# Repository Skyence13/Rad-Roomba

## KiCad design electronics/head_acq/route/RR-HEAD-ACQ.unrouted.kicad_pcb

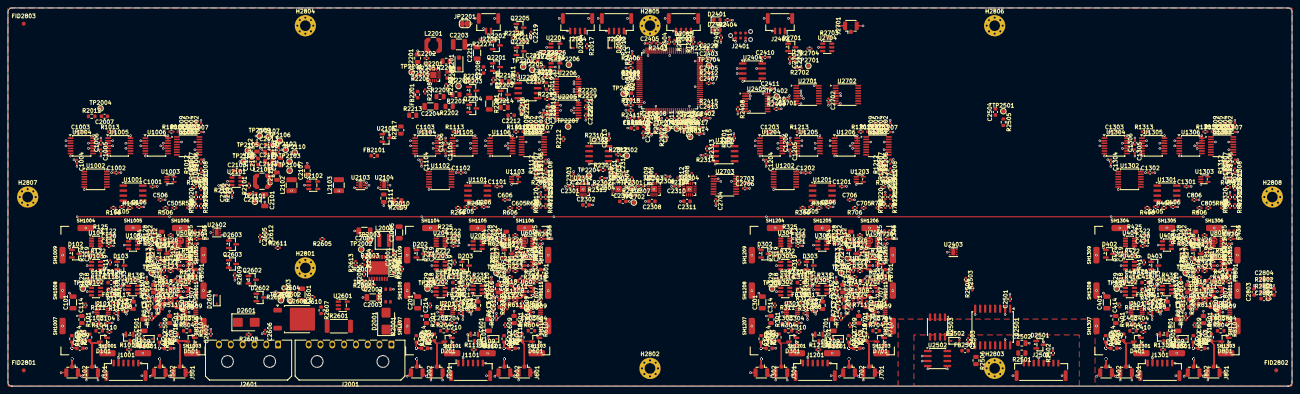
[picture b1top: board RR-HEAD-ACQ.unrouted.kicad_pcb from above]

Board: 6 copper layers, 326.0 x 96.0 mm, 1085 parts (0 on the bottom side), 581 nets.

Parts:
C101, C201, C301, C401, C501, C601, C701, C801, C2204, C2213: 1uF; C_1206_3216Metric
C102, C202, C302, C402, C502, C602, C702, C802, C2001, C2102, C2103, C2205: 100nF; C_0603_1608Metric
C103, C111, C203, C211, C303, C311, C403, C411, C503, C511, C603, C611, C703, C711, C803, C811, C2108, C2406: 4.7uF; C_0603_1608Metric
C104, C105, C106, C107, C108, C113, C114, C115, C118, C120, C121, C122, C125, C126, C127, C204, C205, C206, C207, C208, C213, C214, C215, C218, C220, C221, C222, C225, C226, C227, C304, C305, C306, C307, C308, C313, C314, C315, C318, C320, C321, C322, C325, C326, C327, C404, C405, C406, C407, C408, C413, C414, C415, C418, C420, C421, C422, C425, C426, C427, C504, C505, C506, C507, C508, C513, C514, C515, C518, C520, C521, C522, C604, C605, C606, C607, C608, C613, C614, C615, C618, C620, C621, C622, C704, C705, C706, C707, C708, C713, C714, C715, C718, C720, C721, C722, C804, C805, C806, C807, C808, C813, C814, C815, C818, C820, C821, C822, C1001, C1002, C1003, C1004, C1005, C1006, C1007, C1008, C1009, C1101, C1102, C1103, C1104, C1105, C1106, C1107, C1108, C1109, C1201, C1202, C1203, C1204, C1205, C1206, C1207, C1208, C1209, C1301, C1302, C1303, C1304, C1305, C1306, C1307, C1308, C1309, C2006, C2008, C2009, C2010, C2116, C2202, C2209, C2211, C2216, C2217, C2218, C2219, C2220, C2221, C2222, C2301, C2303, C2304, C2306, C2307, C2309, C2310, C2312, C2313, C2315, C2401, C2402, C2403, C2404, C2405, C2407, C2408, C2409, C2410, C2411, C2412, C2413, C2501, C2503, C2602, C2603, C2606, C2701, C2702, C2703, C2704, C2706: 100nF; C_0402_1005Metric
C109, C209, C309, C409, C509, C609, C709, C809, C1010, C1110, C1210, C1310, C2707, C2708: 100pF; C_0402_1005Metric
C110, C123, C210, C223, C310, C323, C410, C423, C510, C610, C710, C810: 1nF; C_0402_1005Metric
C112, C116, C212, C216, C312, C316, C412, C416, C512, C516, C612, C616, C712, C716, C812, C816, C2109, C2110, C2112, C2201, C2502: 10uF; C_0805_2012Metric
C117, C217, C317, C417, C517, C617, C717, C817: 220pF; C_0402_1005Metric
C119, C219, C319, C419, C519, C619, C719, C819, C2106: 10pF; C_0402_1005Metric
C124, C224, C324, C424: 4.7nF; C_0402_1005Metric
C2002: 22nF; C_0402_1005Metric
C2003, C2004, C2005, C2601: 10uF; C_1206_3216Metric
C2007, C2504, C2801, C2802, C2803, C2804: 10nF; C_0603_1608Metric
C2101: 4.7uF; C_1206_3216Metric
C2104, C2105, C2107, C2111: 22uF; C_0805_2012Metric
C2113, C2115, C2302, C2305, C2308, C2311, C2314: 1uF; C_0603_1608Metric
C2114, C2206, C2207, C2214, C2215, C2604, C2605, C2705: 10nF; C_0402_1005Metric
C2203: 2.2uF; C_1210_3225Metric
C2208: 1nF; C_0603_1608Metric
C2210, C2212: 470nF; C_0603_1608Metric
D101, D201, D301, D401, D501, D601, D701, D801: BAV99; SOT-23
D102, D103, D202, D203, D302, D303, D402, D403, D502, D602, D702, D802, D2603, D2701: BAT54S; SOT-23
D1001, D1101, D1201, D1301, D2002, D2003, D2004, D2502, D2604: PESD5V0S1BA; D_SOD-323
D2001, D2601: SMBJ16A; D_SMB
D2201: PMEG10010ELR; D_SOD-123F
D2202, D2602: BZX84-C12; SOT-23
D2203: BAV199; SOT-23
D2401: green; LED_0603_1608Metric
D2402: red; LED_0603_1608Metric
D2501: SM712; SOT-23
FB101, FB201, FB301, FB401, FB501, FB601, FB701, FB801, FB2101, FB2401: 600R @100MHz; L_0603_1608Metric
FB2201, FB2501: 220R @100MHz; L_0603_1608Metric
FID2801, FID2802, FID2803: fiducial; Fiducial_1mm_Mask2mm
H2801: H1; MountingHole_2.7mm_M2.5_Pad_Via
H2802: H2; MountingHole_2.7mm_M2.5_Pad_Via
H2803: H3; MountingHole_2.7mm_M2.5_Pad_Via
H2804: H4; MountingHole_2.7mm_M2.5_Pad_Via
H2805: H5; MountingHole_2.7mm_M2.5_Pad_Via
H2806: H6; MountingHole_2.7mm_M2.5_Pad_Via
H2807: H7; MountingHole_2.7mm_M2.5_Pad_Via
H2808: H8; MountingHole_2.7mm_M2.5_Pad_Via
J101, J102, J201, J202, J301, J302, J401, J402, J501, J502, J601, J602, J701, J702, J801, J802, J2701: U.FL; U.FL_Hirose_U.FL-R-SMT-1_Vertical
J1001, J1101, J1201, J1301: GH-6; JST_GH_SM06B-GHS-TB_1x06-1MP_P1.25mm_Horizontal
J2001: Micro-Fit 3.0 1x8 RA; Molex_Micro-Fit_3.0_43650-0800_1x08_P3.00mm_Horizontal
J2002, J2003, J2004: GH-4; JST_GH_SM04B-GHS-TB_1x04-1MP_P1.25mm_Horizontal
J2201: GH-2; JST_GH_SM02B-GHS-TB_1x02-1MP_P1.25mm_Horizontal
J2401: TC2030-NL; Tag-Connect_TC2030-IDC-NL_2x03_P1.27mm_Vertical
J2402: GH-3; JST_GH_SM03B-GHS-TB_1x03-1MP_P1.25mm_Horizontal
J2501: GH-8; JST_GH_SM08B-GHS-TB_1x08-1MP_P1.25mm_Horizontal
J2601: Micro-Fit 3.0 1x6 RA; Molex_Micro-Fit_3.0_43650-0600_1x06_P3.00mm_Horizontal
JP2201: open; SolderJumper-2_P1.3mm_Open_RoundedPad1.0x1.5mm
L2001: 900R CM; L_CommonMode_TDK_ACM4520
L2002: 10uH; L_Coilcraft_XAL4040-XXX
L2101, L2201: 10uH; L_Coilcraft_LPS4018
L2102, L2103: 10uH; L_1210_3225Metric
Q1001, Q1101, Q1201, Q1301, Q2205, Q2602: BSS138; SOT-23
Q2201, Q2203, Q2204: BSS123; SOT-23
Q2202: MMBTA42; SOT-23
Q2601: SUD50P04-08; TO-252-2
Q2603: MMBT3904; SOT-23
R101, R201, R301, R401, R501, R601, R701, R801: 1k; R_0805_2012Metric
R102, R202, R302, R402, R502, R602, R702, R802: 100R; R_0603_1608Metric
R103, R104, R203, R204, R303, R304, R403, R404, R503, R504, R603, R604, R703, R704, R803, R804: 20R; R_0603_1608Metric
R105, R205, R305, R405, R505, R605, R705, R805: 4.99k; R_0402_1005Metric
R106, R206, R306, R406, R506, R606, R706, R806: 220k; R_0402_1005Metric
R107, R109, R115, R119, R125, R126, R127, R129, R134, R135, R207, R209, R215, R219, R225, R226, R227, R229, R234, R235, R307, R309, R315, R319, R325, R326, R327, R329, R334, R335, R407, R409, R415, R419, R425, R426, R427, R429, R434, R435, R507, R509, R515, R519, R525, R526, R527, R607, R609, R615, R619, R625, R626, R627, R707, R709, R715, R719, R725, R726, R727, R807, R809, R815, R819, R825, R826, R827, R1015, R1115, R1215, R1315, R2013, R2015, R2017, R2207, R2220, R2404, R2405, R2602, R2605, R2701, R2704: 1k; R_0402_1005Metric
R108, R130, R208, R230, R308, R330, R408, R430, R508, R608, R708, R808, R1013, R1014, R1016, R1018, R1113, R1114, R1116, R1118, R1213, R1214, R1216, R1218, R1313, R1314, R1316, R1318, R2011, R2014, R2016, R2018, R2103, R2206, R2210, R2211, R2216, R2222, R2224, R2226, R2228, R2229, R2231, R2302, R2304, R2306, R2308, R2310, R2313, R2314, R2401, R2409, R2410, R2411, R2412, R2503, R2504, R2606, R2613: 10k; R_0402_1005Metric
R110, R113, R121, R128, R210, R213, R221, R228, R310, R313, R321, R328, R410, R413, R421, R428, R510, R513, R521, R528, R610, R613, R621, R628, R710, R713, R721, R728, R810, R813, R821, R828, R1017, R1019, R1117, R1119, R1217, R1219, R1317, R1319: 100R; R_0402_1005Metric
R111, R211, R311, R411, R511, R611, R711, R811, R2703: 49.9R; R_0402_1005Metric
R112, R212, R312, R412, R512, R612, R712, R812, R1002, R1004, R1006, R1008, R1010, R1011, R1012, R1020, R1102, R1104, R1106, R1108, R1110, R1111, R1112, R1120, R1202, R1204, R1206, R1208, R1210, R1211, R1212, R1220, R1302, R1304, R1306, R1308, R1310, R1311, R1312, R1320, R2008, R2101, R2212, R2227, R2230, R2309, R2315, R2316, R2403, R2408, R2413, R2414, R2415, R2416, R2417, R2608, R2610, R2612, R2702: 100k; R_0402_1005Metric
R114, R214, R314, R414, R514, R614, R714, R814: 22R; R_0402_1005Metric
R116, R122, R132, R216, R222, R232, R316, R322, R332, R416, R422, R432, R516, R522, R616, R622, R716, R722, R816, R822: 499R; R_0402_1005Metric
R117, R123, R217, R223, R317, R323, R417, R423, R517, R523, R617, R623, R717, R723, R817, R823: 24.9R; R_0402_1005Metric
R118, R218, R318, R418, R518, R618, R718, R818: 453R; R_0402_1005Metric
R120, R220, R320, R420, R520, R620, R720, R820: 226R; R_0402_1005Metric
R124, R133, R224, R233, R324, R333, R424, R433, R524, R624, R724, R824, R2301, R2303, R2305, R2307: 330R; R_0402_1005Metric
R131, R231, R331, R431: 2k; R_0402_1005Metric
R1001, R1003, R1005, R1007, R1009, R1101, R1103, R1105, R1107, R1109, R1201, R1203, R1205, R1207, R1209, R1301, R1303, R1305, R1307, R1309: 47R; R_0402_1005Metric
R2001: 4.7k; R_0603_1608Metric
R2002: 866k; R_0603_1608Metric
R2003: 68.1k; R_0402_1005Metric
R2004: 66.5k; R_0402_1005Metric
R2005: 12k; R_0402_1005Metric
R2006: 30.1k; R_0402_1005Metric
R2007, R2502: 0R; R_0402_1005Metric
R2009: 1R; R_0805_2012Metric
R2010: 56k; R_0402_1005Metric
R2012, R2505, R2802: 1M; R_0603_1608Metric
R2019: 1k; R_0603_1608Metric
R2102: 60.4k; R_0402_1005Metric
R2201, R2202: 1.07M; R_0805_2012Metric
R2203: 71.5k; R_0402_1005Metric
R2204: 100R; R_0805_2012Metric
R2205: 49.9k; R_0402_1005Metric
R2208: 2.49k; R_0402_1005Metric
R2209: 470k; R_0805_2012Metric
R2213, R2214: 1.2M; R_0805_2012Metric
R2215: 100k; R_0603_1608Metric
R2217, R2218: 4.99M; R_0805_2012Metric
R2219: 412k; R_0402_1005Metric
R2221: 47k; R_1206_3216Metric
R2223: 7.15k; R_0402_1005Metric
R2225: 18.7k; R_0402_1005Metric
R2311: 3.16k; R_0402_1005Metric
R2312: 10R; R_0402_1005Metric
R2402: 33R; R_0402_1005Metric
R2406, R2407: 2.2k; R_0402_1005Metric
R2501, R2506: 120R; R_0805_2012Metric
R2601: 10mR; R_2512_6332Metric
R2603: 68k; R_0402_1005Metric
R2604, R2609: 47k; R_0402_1005Metric
R2607: 47k; R_0603_1608Metric
R2611: 33k; R_0402_1005Metric
R2801: 0R; R_0603_1608Metric
RT2201: 10k NTC; R_0402_1005Metric
SH1001, SH1002, SH1003, SH1004, SH1005, SH1006, SH1007, SH1008, SH1009, SH1010, SH1011, SH1012, SH1101, SH1102, SH1103, SH1104, SH1105, SH1106, SH1107, SH1108, SH1109, SH1110, SH1111, SH1112, SH1201, SH1202, SH1203, SH1204, SH1205, SH1206, SH1207, SH1208, SH1209, SH1210, SH1211, SH1212, SH1301, SH1302, SH1303, SH1304, SH1305, SH1306, SH1307, SH1308, SH1309, SH1310, SH1311, SH1312: shield clip; Harwin_S1711-46R_ShieldClip
SH1013, SH1113, SH1213, SH1313: lane shield can; RR-HEAD-SHLD-A_LaneShieldCan
TP101: F0 PRE; TestPoint_Pad_D1.0mm
TP201: F1 PRE; TestPoint_Pad_D1.0mm
TP301: F2 PRE; TestPoint_Pad_D1.0mm
TP401: F3 PRE; TestPoint_Pad_D1.0mm
TP501: R0 PRE; TestPoint_Pad_D1.0mm
TP601: R1 PRE; TestPoint_Pad_D1.0mm
TP701: R2 PRE; TestPoint_Pad_D1.0mm
TP801: R3 PRE; TestPoint_Pad_D1.0mm
TP2001: EF_IMON; TestPoint_Pad_D1.0mm
TP2002: EF_SHDN; TestPoint_Pad_D1.0mm
TP2003: EF_MODE; TestPoint_Pad_D1.0mm
TP2004: J1 SHIELD; TestPoint_Pad_D1.0mm
TP2101: VIN_F; TestPoint_Pad_D1.0mm
TP2102: +5V6; TestPoint_Pad_D1.0mm
TP2103: +5V_A; TestPoint_Pad_D1.0mm
TP2104: +3V3; TestPoint_Pad_D1.0mm
TP2105: +3V3_EVT; TestPoint_Pad_D1.0mm
TP2106: VREF_ADC; TestPoint_Pad_D1.0mm
TP2107, TP2108, TP2109, TP2110: GND; TestPoint_Pad_D1.0mm
TP2201: HV_MON2; TestPoint_Pad_D1.0mm
TP2202: HV_BUS; TestPoint_Pad_D1.0mm
TP2203: HV_RAW; TestPoint_Pad_D1.0mm
TP2204: HV_SET; TestPoint_Pad_D1.0mm
TP2205: HV_DRV; TestPoint_Pad_D1.0mm
TP2206: HV_INH_N; TestPoint_Pad_D1.0mm
TP2207: HV_PERMIT; TestPoint_Pad_D1.0mm
TP2208: BIAS_VMON; TestPoint_Pad_D1.0mm
TP2209: BIAS_IMON; TestPoint_Pad_D1.0mm
TP2301: DAC1 OUT7; TestPoint_Pad_D1.0mm
TP2302: VBL; TestPoint_Pad_D1.0mm
TP2401: BOOT0; TestPoint_Pad_D1.0mm
TP2402: EXP P7; TestPoint_Pad_D1.0mm
TP2403: SYNC_IN; TestPoint_Pad_D1.0mm
TP2501: J2 SHIELD; TestPoint_Pad_D1.0mm
TP2601: HTR_SW; TestPoint_Pad_D1.0mm
TP2602: HTR_GATE; TestPoint_Pad_D1.0mm
TP2701: MON_BUS; TestPoint_Pad_D1.0mm
TP2702: PULSER_AMPL; TestPoint_Pad_D1.0mm
TP2703: PULSER_STROBE; TestPoint_Pad_D1.0mm
TP2704: LATCH_TEST; TestPoint_Pad_D1.0mm
U101, U201, U301, U401, U501, U601, U701, U801: 74LVC2G53; VSSOP-8_2.3x2mm_P0.5mm
U102, U103, U202, U203, U302, U303, U402, U403, U502, U503, U602, U603, U702, U703, U802, U803: OPA838; SOT-23-6
U104, U204, U304, U404, U504, U604, U704, U804: TLV3502; SOT-23-8
U105, U205, U305, U405, U2704: OPA836; SOT-23-6
U106, U206, U306, U406: TLV3501; SOT-23-6
U1001, U1101, U1201, U1301, U2305, U2306: TLV9062; SOIC-8_3.9x4.9mm_P1.27mm
U1002, U1102, U1202, U1302: 74LVC32A; TSSOP-14_4.4x5mm_P0.65mm
U1003, U1103, U1203, U1303: 74LVC1G32; SOT-353_SC-70-5
U1004, U1005, U1006, U1104, U1105, U1106, U1204, U1205, U1206, U1304, U1305, U1306, U2205: 74LVC74A; TSSOP-14_4.4x5mm_P0.65mm
U1007, U1107, U1207, U1307, U2703: TMUX1108; TSSOP-16_4.4x5mm_P0.65mm
U2001: TPS26600; HTSSOP-16-1EP_4.4x5mm_P0.65mm_EP3.4x5mm
U2101: LMR51606YF; SOT-23-6
U2102: TPS7A2050; SOT-23-5
U2103, U2104: TLV76733; WSON-6-1EP_2x2mm_P0.65mm_EP1x1.6mm
U2105: REF3030; SOT-23
U2201: TPS61391; WQFN-16-1EP_3x3mm_P0.5mm_EP1.6x1.6mm
U2202: OPA2333; SOIC-8_3.9x4.9mm_P1.27mm
U2203, U2204: TLV7021; SOT-23-5
U2206: 74LVC00A; TSSOP-14_4.4x5mm_P0.65mm
U2301, U2302, U2303, U2304: DAC60508Z; WQFN-16-1EP_3x3mm_P0.5mm_EP1.6x1.6mm
U2401: STM32G474VET6; LQFP-100_14x14mm_P0.5mm
U2402, U2403: TMP117; WSON-6-1EP_2x2mm_P0.65mm_EP1x1.6mm
U2404: 24AA025E64; SOIC-8_3.9x4.9mm_P1.27mm
U2405: TCA9534; TSSOP-16_4.4x5mm_P0.65mm
U2501: ISO1430B; SOIC-16W_7.5x10.3mm_P1.27mm
U2502: THVD1420; SOIC-8_3.9x4.9mm_P1.27mm
U2503: ISO7710; SOIC-8_3.9x4.9mm_P1.27mm
U2601: INA180A2; SOT-23-5
U2701: 74HC238; TSSOP-16_4.4x5mm_P0.65mm
U2702: 74LVC138A; TSSOP-16_4.4x5mm_P0.65mm
Y2401: 24.000 MHz TCXO; Oscillator_SMD_ECS_2520MV-xxx-xx-4Pin_2.5x2.0mm

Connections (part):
+3V3: C2110.1, C2216.1, C2217.1, C2220.1, C2221.1, C2303.1, C2306.1, C2309.1, C2312.1, C2401.1, C2402.1, C2403.1, C2404.1, C2405.1, C2406.1, C2410.1, C2411.1, C2412.1, C2413.1, C2501.1, C2602.1, C2701.1, D2603.2, FB2101.1, FB2201.1, FB2401.1, J2401.1, R1017.1, R1117.1, R1217.1, R1317.1, R2008.1, R2014.1, R2016.1, R2018.1, R2226.1, R2227.1, R2302.1, R2304.1, R2306.1, R2308.1, R2309.1, R2403.1, R2404.1, R2405.1, R2406.1, R2407.1, R2503.1, TP2104.1, U2103.1, U2103.2, U2203.5, U2204.5, U2205.2, U2205.4, U2205.10, U2205.13, U2205.14, U2206.14, U2301.16, U2302.16, U2303.16, U2304.16, U2401.6, U2401.24, U2401.49, U2401.64, U2401.75, U2401.100, U2402.5, U2403.4, U2403.5, U2404.8, U2405.16, U2501.1, U2503.8, U2601.5, U2701.6, U2701.16, U2703.2
+3V3A: C2113.1, C2114.1, C2407.1, D2701.2, FB2101.2, U2105.1, U2401.37
+3V3_EVT: C107.1, C122.1, C127.1, C207.1, C222.1, C227.1, C307.1, C322.1, C327.1, C407.1, C422.1, C427.1, C507.1, C522.1, C607.1, C622.1, C707.1, C722.1, C807.1, C822.1, C1002.1, C1003.1, C1004.1, C1005.1, C1006.1, C1102.1, C1103.1, C1104.1, C1105.1, C1106.1, C1202.1, C1203.1, C1204.1, C1205.1, C1206.1, C1302.1, C1303.1, C1304.1, C1305.1, C1306.1, C2112.1, C2702.1, D102.2, D103.2, D202.2, D203.2, D302.2, D303.2, D402.2, D403.2, D502.2, D602.2, D702.2, D802.2, TP2105.1, U101.8, U104.8, U106.4, U201.8, U204.8, U206.4, U301.8, U304.8, U306.4, U401.8, U404.8, U406.4, U501.8, U504.8, U601.8, U604.8, U701.8, U704.8, U801.8, U804.8, U1002.14, U1003.5, U1004.2, U1004.4, U1004.10, U1004.12, U1004.14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
+3V3_HV: C2201.1, C2202.1, FB2201.2, L2201.1, U2201.10, U2201.14, U2201.15
+5V6: C2104.1, C2105.1, C2106.1, C2109.1, L2101.2, L2102.1, L2103.1, R2102.1, TP2102.1, U2103.4, U2103.6
+5V6_A: C2107.1, L2102.2, U2102.1, U2102.3
+5V6_E: C2111.1, L2103.2, U2104.4, U2104.6
+5V_A: C1001.1, C1007.1, C1101.1, C1107.1, C1201.1, C1207.1, C1301.1, C1307.1, C2108.1, C2209.1, C2302.1, C2305.1, C2308.1, C2311.1, C2313.1, C2315.1, C2703.1, C2706.1, D101.2, D201.2, D301.2, D401.2, D501.2, D601.2, D701.2, D801.2, D2203.2, FB101.1, FB201.1, FB301.1, FB401.1, FB501.1, FB601.1, FB701.1, FB801.1, R2224.1, TP2103.1, U1001.8, U1007.13, U1101.8, U1107.13, U1201.8, U1207.13, U1301.8, U1307.13, U2102.5, U2202.8, U2301.7, U2302.7, U2303.7, U2304.7, U2305.8, U2306.8, U2703.13, U2704.5, U2704.6
ALPHA_F0: R1005.2, R1006.1, U2401.86
ALPHA_F1: R1105.2, R1106.1, U2401.87
ALPHA_F2: R1205.2, R1206.1, U2401.88
ALPHA_F3: R1305.2, R1306.1, U2401.89
BIAS_IMON: C2207.1, R2207.2, TP2209.1, U2401.25
BIAS_IMON_R: C2206.1, R2206.1, R2207.1, U2201.4
BIAS_VMON: C2215.1, R2220.2, TP2208.1, U2401.22
BIAS_VMON_B: R2220.1, U2202.6, U2202.7, U2203.4
BK_CB: C2103.1, U2101.1
BK_EN: R2101.2, U2101.4
BK_FB: C2106.2, R2102.2, R2103.1, U2101.3
BK_SW: C2103.2, L2101.1, U2101.6
BOOT0: R2401.1, TP2401.1, U2401.95
BUMP_ZONE_F_N: C2008.1, R2013.2, R2014.2, U2401.7
BUMP_ZONE_L_N: C2009.1, R2015.2, R2016.2, U2401.8
BUMP_ZONE_R_N: C2010.1, R2017.2, R2018.2, U2401.9
BUSY_F0: R1001.2, R1002.1, U2401.78
BUSY_F1: R1101.2, R1102.1, U2401.90
BUSY_F2: R1201.2, R1202.1, U2401.47
BUSY_F3: R1301.2, R1302.1, U2401.50
BUSY_R0: R1007.2, R1008.1, U2401.20
BUSY_R1: R1107.2, R1108.1, U2401.21
BUSY_R2: R1207.2, R1208.1, U2401.39
BUSY_R3: R1307.2, R1308.1, U2401.40
BUS_5V: D2502.1, FB2501.1, J2501.3
BUS_5VF: C2502.1, C2503.1, FB2501.2, U2501.16, U2502.8, U2503.1
BUS_GND: C2502.2, C2503.2, D2501.3, D2502.2, J2501.4, J2501.MP, R2502.2, U2501.9, U2501.15, U2502.2, U2502.3, U2502.4, U2502.5, U2503.4
BZ_F_IN: D2002.1, J2002.3, R2013.1
BZ_L_IN: D2003.1, J2003.3, R2015.1
BZ_R_IN: D2004.1, J2004.3, R2017.1
CLR_F0_N: R1013.1, U1004.1, U1004.13, U1005.1, U2401.97
CLR_F1_N: R1113.1, U1104.1, U1104.13, U1105.1, U2401.98
CLR_F2_N: R1213.1, U1204.1, U1204.13, U1205.1, U2401.5
CLR_F3_N: R1313.1, U1304.1, U1304.13, U1305.1, U2401.38
CLR_R0_N: R1014.1, U1005.13, U1006.1, U2401.41
CLR_R1_N: R1114.1, U1105.13, U1106.1, U2401.42
CLR_R2_N: R1214.1, U1205.13, U1206.1, U2401.43
CLR_R3_N: R1314.1, U1305.13, U1306.1, U2401.44
DAC0_REF: C2301.1, U2301.1
DAC0_SDO: R2301.1, U2301.15
DAC1_REF: C2304.1, U2302.1, U2305.3
DAC1_SDO: R2303.1, U2302.15
DAC1_SPARE: TP2301.1, U2302.11
DAC2_REF: C2307.1, U2303.1
DAC2_SDO: R2305.1, U2303.15
DAC3_REF: C2310.1, U2304.1
DAC3_SDO: R2307.1, U2304.15
DAC_CS0_N: R2302.2, U2301.12, U2401.26
DAC_CS1_N: R2304.2, U2302.12, U2401.31
DAC_CS2_N: R2306.2, U2303.12, U2401.34
DAC_CS3_N: R2308.2, U2304.12, U2401.66
DAC_MISO: R2301.2, R2303.2, R2305.2, R2307.2, R2309.2, U2401.28
DAC_MOSI: U2301.14, U2302.14, U2303.14, U2304.14, U2401.29
DAC_SCK: U2301.13, U2302.13, U2303.13, U2304.13, U2401.27
DBG_RX: J2402.2, R2403.2, U2401.80
DBG_TX: J2402.1, U2401.79
EF_DVDT: C2002.1, U2001.12
EF_FLT_N: R2008.2, U2001.14, U2405.9
EF_ILIM: R2005.1, U2001.11
EF_IMON: R2006.1, TP2001.1, U2001.10
EF_MODE: R2007.1, TP2003.1, U2001.6
EF_OVP: R2003.2, R2004.1, U2001.5
EF_RTN: C2002.2, R2004.2, R2005.2, R2006.2, R2007.2, U2001.8, U2001.17
EF_SHDN: TP2002.1, U2001.7
EF_UVLO: R2002.2, R2003.1, U2001.3
EXP_P7: TP2402.1, U2405.12
F0_A: C109.2, C110.2, D101.3, J101.1, R103.1, R104.1, R114.1
F0_CALPHA: U106.5, U1002.9
F0_CLLD: R128.1, U104.7, U1002.1
F0_CULD: U104.6, U1002.4
F0_FAST: C119.1, R122.1, R124.1, U103.1
F0_FCMP: D102.3, R124.2, R125.1, U104.1, U104.3
F0_FFB: C119.2, R122.2, R123.1, U103.4
F0_FS: C117.2, R120.2, R121.1, U103.3
F0_HV1: C101.1, R101.2, R102.1
F0_HVF: C102.1, J102.1, R102.2
F0_KALPHA: U1002.8, U1005.3
F0_KLLD: U1002.3, U1004.3
F0_KULD: U1002.6, U1004.11
F0_MFAST: R125.2, U1007.4
F0_MPRE: R119.2, U1007.12
F0_MSLOW: R134.2, U1007.6
F0_PFB: R116.2, R117.1, U102.4
F0_PG: C116.1, R117.2
F0_PIN: C114.2, R115.1, U102.3
F0_PINA: C114.1, R114.2
F0_PRE: C117.1, R116.1, R118.1, R119.1, R120.1, R129.1, U102.1
F0_PRE_TP: R118.2, TP101.1
F0_SCMP: D103.3, R133.2, R134.1, U106.3
F0_SFB: R131.2, R132.1, U105.4
F0_SI: C123.1, C124.1, R129.2
F0_SLOW: R131.1, R133.1, U105.1
F0_SS: C124.2, R130.1, U105.3
F0_TA: C126.1, R135.2, U106.1
F0_TL: C120.1, R126.2, U104.2
F0_TPG: R110.1, U101.7
F0_TPI: C109.1, C110.1, R111.2
F0_TPSW: R111.1, R112.1, U101.1
F0_TPV: C108.1, R109.2, U101.6
F0_TRIM: C103.1, C104.1, R103.2, R104.2, R105.2, R106.1
F0_TRIMDRV: C105.1, R105.1, R108.1, U1001.1
F0_TRIMFB: C105.2, R106.2, U1001.2
F0_TRIMIN: C106.1, R107.2, U1001.3
F0_TU: C121.1, R127.2, U104.4
F0_V5: C111.1, C115.1, C118.1, C125.1, FB101.2, U102.5, U102.6, U103.5, U103.6, U105.5, U105.6
F0_VBL: C112.1, C113.1, R113.2, R115.2, R121.2, R123.2, R130.2, R132.2, R1015.1
F1_A: C209.2, C210.2, D201.3, J201.1, R203.1, R204.1, R214.1
F1_CALPHA: U206.5, U1102.9
F1_CLLD: R228.1, U204.7, U1102.1
F1_CULD: U204.6, U1102.4
F1_FAST: C219.1, R222.1, R224.1, U203.1
F1_FCMP: D202.3, R224.2, R225.1, U204.1, U204.3
F1_FFB: C219.2, R222.2, R223.1, U203.4
F1_FS: C217.2, R220.2, R221.1, U203.3
F1_HV1: C201.1, R201.2, R202.1
F1_HVF: C202.1, J202.1, R202.2
F1_KALPHA: U1102.8, U1105.3
F1_KLLD: U1102.3, U1104.3
F1_KULD: U1102.6, U1104.11
F1_MFAST: R225.2, U1107.4
F1_MPRE: R219.2, U1107.12
F1_MSLOW: R234.2, U1107.6
F1_PFB: R216.2, R217.1, U202.4
F1_PG: C216.1, R217.2
F1_PIN: C214.2, R215.1, U202.3
F1_PINA: C214.1, R214.2
F1_PRE: C217.1, R216.1, R218.1, R219.1, R220.1, R229.1, U202.1
F1_PRE_TP: R218.2, TP201.1
F1_SCMP: D203.3, R233.2, R234.1, U206.3
F1_SFB: R231.2, R232.1, U205.4
F1_SI: C223.1, C224.1, R229.2
F1_SLOW: R231.1, R233.1, U205.1
F1_SS: C224.2, R230.1, U205.3
F1_TA: C226.1, R235.2, U206.1
F1_TL: C220.1, R226.2, U204.2
F1_TPG: R210.1, U201.7
F1_TPI: C209.1, C210.1, R211.2
F1_TPSW: R211.1, R212.1, U201.1
F1_TPV: C208.1, R209.2, U201.6
F1_TRIM: C203.1, C204.1, R203.2, R204.2, R205.2, R206.1
F1_TRIMDRV: C205.1, R205.1, R208.1, U1101.1
F1_TRIMFB: C205.2, R206.2, U1101.2
F1_TRIMIN: C206.1, R207.2, U1101.3
F1_TU: C221.1, R227.2, U204.4
F1_V5: C211.1, C215.1, C218.1, C225.1, FB201.2, U202.5, U202.6, U203.5, U203.6, U205.5, U205.6
F1_VBL: C212.1, C213.1, R213.2, R215.2, R221.2, R223.2, R230.2, R232.2, R1115.1
F2_A: C309.2, C310.2, D301.3, J301.1, R303.1, R304.1, R314.1
F2_CALPHA: U306.5, U1202.9
F2_CLLD: R328.1, U304.7, U1202.1
F2_CULD: U304.6, U1202.4
F2_FAST: C319.1, R322.1, R324.1, U303.1
F2_FCMP: D302.3, R324.2, R325.1, U304.1, U304.3
F2_FFB: C319.2, R322.2, R323.1, U303.4
F2_FS: C317.2, R320.2, R321.1, U303.3
F2_HV1: C301.1, R301.2, R302.1
F2_HVF: C302.1, J302.1, R302.2
F2_KALPHA: U1202.8, U1205.3
F2_KLLD: U1202.3, U1204.3
F2_KULD: U1202.6, U1204.11
F2_MFAST: R325.2, U1207.4
F2_MPRE: R319.2, U1207.12
F2_MSLOW: R334.2, U1207.6
F2_PFB: R316.2, R317.1, U302.4
F2_PG: C316.1, R317.2
F2_PIN: C314.2, R315.1, U302.3
F2_PINA: C314.1, R314.2
F2_PRE: C317.1, R316.1, R318.1, R319.1, R320.1, R329.1, U302.1
F2_PRE_TP: R318.2, TP301.1
F2_SCMP: D303.3, R333.2, R334.1, U306.3
F2_SFB: R331.2, R332.1, U305.4
F2_SI: C323.1, C324.1, R329.2
F2_SLOW: R331.1, R333.1, U305.1
F2_SS: C324.2, R330.1, U305.3
F2_TA: C326.1, R335.2, U306.1
F2_TL: C320.1, R326.2, U304.2
F2_TPG: R310.1, U301.7
F2_TPI: C309.1, C310.1, R311.2
F2_TPSW: R311.1, R312.1, U301.1
F2_TPV: C308.1, R309.2, U301.6
F2_TRIM: C303.1, C304.1, R303.2, R304.2, R305.2, R306.1
F2_TRIMDRV: C305.1, R305.1, R308.1, U1201.1
F2_TRIMFB: C305.2, R306.2, U1201.2
F2_TRIMIN: C306.1, R307.2, U1201.3
F2_TU: C321.1, R327.2, U304.4
F2_V5: C311.1, C315.1, C318.1, C325.1, FB301.2, U302.5, U302.6, U303.5, U303.6, U305.5, U305.6
F2_VBL: C312.1, C313.1, R313.2, R315.2, R321.2, R323.2, R330.2, R332.2, R1215.1
F3_A: C409.2, C410.2, D401.3, J401.1, R403.1, R404.1, R414.1
F3_CALPHA: U406.5, U1302.9
F3_CLLD: R428.1, U404.7, U1302.1
F3_CULD: U404.6, U1302.4
F3_FAST: C419.1, R422.1, R424.1, U403.1
F3_FCMP: D402.3, R424.2, R425.1, U404.1, U404.3
F3_FFB: C419.2, R422.2, R423.1, U403.4
F3_FS: C417.2, R420.2, R421.1, U403.3
F3_HV1: C401.1, R401.2, R402.1
F3_HVF: C402.1, J402.1, R402.2
F3_KALPHA: U1302.8, U1305.3
F3_KLLD: U1302.3, U1304.3
F3_KULD: U1302.6, U1304.11
F3_MFAST: R425.2, U1307.4
F3_MPRE: R419.2, U1307.12
F3_MSLOW: R434.2, U1307.6
F3_PFB: R416.2, R417.1, U402.4
F3_PG: C416.1, R417.2
F3_PIN: C414.2, R415.1, U402.3
F3_PINA: C414.1, R414.2
F3_PRE: C417.1, R416.1, R418.1, R419.1, R420.1, R429.1, U402.1
F3_PRE_TP: R418.2, TP401.1
F3_SCMP: D403.3, R433.2, R434.1, U406.3
F3_SFB: R431.2, R432.1, U405.4
F3_SI: C423.1, C424.1, R429.2
F3_SLOW: R431.1, R433.1, U405.1
F3_SS: C424.2, R430.1, U405.3
F3_TA: C426.1, R435.2, U406.1
F3_TL: C420.1, R426.2, U404.2
F3_TPG: R410.1, U401.7
F3_TPI: C409.1, C410.1, R411.2
F3_TPSW: R411.1, R412.1, U401.1
F3_TPV: C408.1, R409.2, U401.6
F3_TRIM: C403.1, C404.1, R403.2, R404.2, R405.2, R406.1
F3_TRIMDRV: C405.1, R405.1, R408.1, U1301.1
F3_TRIMFB: C405.2, R406.2, U1301.2
F3_TRIMIN: C406.1, R407.2, U1301.3
F3_TU: C421.1, R427.2, U404.4
F3_V5: C411.1, C415.1, C418.1, C425.1, FB401.2, U402.5, U402.6, U403.5, U403.6, U405.5, U405.6
F3_VBL: C412.1, C413.1, R413.2, R415.2, R421.2, R423.2, R430.2, R432.2, R1315.1
FRAME: C2007.2, C2504.2, C2801.1, C2802.1, C2803.1, C2804.1, H2801.1, H2802.1, H2803.1, H2804.1, H2805.1, H2806.1, H2807.1, H2808.1, R2012.2, R2505.2, R2801.1, R2802.1
GND: C101.2, C102.2, C103.2, C104.2, C106.2, C107.2, C108.2, C111.2, C112.2, C113.2, C115.2, C116.2, C118.2, C120.2, C121.2, C122.2, C123.2, C125.2, C126.2, C127.2, C201.2, C202.2, C203.2, C204.2, C206.2, C207.2, C208.2, C211.2, C212.2, C213.2, C215.2, C216.2, C218.2, C220.2, C221.2, C222.2, C223.2, C225.2, C226.2, C227.2, C301.2, C302.2, C303.2, C304.2, C306.2, C307.2, C308.2, C311.2, C312.2, C313.2, C315.2, C316.2, C318.2, C320.2, C321.2, C322.2, C323.2, C325.2, C326.2, C327.2, C401.2, C402.2, C403.2, C404.2, C406.2, C407.2, C408.2, C411.2, C412.2, C413.2, C415.2, C416.2, C418.2, C420.2, C421.2, C422.2, C423.2, C425.2, C426.2, C427.2, C501.2, C502.2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
HEAD_HTR_N: C2601.2, D2601.2, J2001.4, J2601.2
HEAD_HTR_P: C2601.1, D2601.1, J2001.3, R2601.1, R2607.1, R2610.1, U2601.3
HEAD_LOOP_OUT: J2001.5, J2002.1
HEAD_LOOP_RET: J2001.6, R2019.2
HEAD_PRES_ID: J2001.7, R2001.1
HEAD_PWR_N: D2001.2, J2001.2, L2001.4, R2001.2
HEAD_PWR_P: D2001.1, J2001.1, L2001.1
HSE_IN_24M: R2402.2, U2401.12
HTR_CQB: Q2603.1, R2608.2, R2609.1
HTR_CUT: J2601.3, R2608.1
HTR_CUTOUT_OK: C2605.1, D2603.3, R2611.2, R2612.1, U2401.72
HTR_CX: Q2603.3, R2610.2, R2611.1
HTR_EN: R2605.1, R2606.1, U2401.54
HTR_ENG: Q2602.1, R2605.2
HTR_GATE: C2604.1, D2602.1, Q2601.1, R2603.2, R2604.1, TP2602.1
HTR_GD: Q2602.3, R2604.2
HTR_PS: D2602.3, Q2601.3, R2601.2, R2603.1, U2601.4
HTR_SENSE: C2603.1, R2602.2, U2401.51
HTR_SENSE_R: R2602.1, U2601.1
HTR_SW: C2604.2, J2601.1, Q2601.2, R2607.2, TP2601.1
HV_B: Q2202.1, R2211.2
HV_BFB: R2202.2, R2203.1, U2201.12
HV_BFBM: R2201.2, R2202.1
HV_BLD: Q2204.3, R2221.2
HV_BUS: C2213.1, D2202.1, Q2201.2, R101.1, R201.1, R301.1, R401.1, R501.1, R601.1, R701.1, R801.1, R2213.1, R2217.1, R2221.1, TP2202.1
HV_CAP: C2205.1, U2201.9
HV_DRV: C2210.1, R2211.1, TP2205.1, U2202.1
HV_E: Q2202.2, R2210.1
HV_EN: R2229.1, U2205.3, U2206.2, U2401.52
HV_FB: C2212.1, D2203.3, R2214.2, R2215.1, U2202.3
HV_FBM: R2213.2, R2214.1
HV_G: C2208.1, D2202.3, Q2201.1, Q2202.3, Q2203.3, R2209.2
HV_INH_N: Q2205.3, R2226.2, TP2206.1, U2203.1, U2204.1, U2205.1, U2405.6
HV_ISHORT: R2205.1, U2201.11
HV_MDIV: C2214.1, R2218.2, R2219.1, U2202.5
HV_MDM: R2217.2, R2218.1
HV_MIR: Q2201.3, U2201.5
HV_MON2: R2208.1, TP2201.1, U2201.3
HV_OFF: Q2203.1, Q2204.1, R2216.1, U2206.3, U2206.4, U2206.5
HV_OFFR: D2203.1, R2216.2
HV_ON: R2230.1, U2201.13, U2206.6
HV_OVP_SET: C2218.1, R2222.2, R2223.1, U2203.3
HV_PERMIT: TP2207.1, U2205.5, U2206.1, U2405.5
HV_PG_DIV: R2224.2, R2225.1, U2204.3
HV_RAW: C2203.1, D2201.1, R2201.1, R2204.1, TP2203.1
HV_RAWF: C2204.1, R2204.2, R2209.1, U2201.6
HV_SET: C2211.1, R2212.1, TP2204.1, U2301.10
HV_SUM: C2210.2, R2212.2, U2202.2
HV_SW: D2201.2, L2201.2, U2201.8
HWREV0: R2409.1, U2405.10
HWREV1: R2410.1, U2405.11
I2C_SCL: R2406.2, U2401.69, U2402.1, U2403.1, U2404.6, U2405.14
I2C_SDA: R2407.2, U2401.68, U2402.6, U2403.6, U2404.5, U2405.15
IMON_BUF: R2701.1, U2306.6, U2306.7
IMON_CH: C2705.1, R2701.2, U2401.46
IMON_F0: R108.2, U2703.4
IMON_F1: R208.2, U2703.5
IMON_F2: R308.2, U2703.6
IMON_F3: R408.2, U2703.7
IMON_MUX: C2704.1, U2306.5, U2703.8
IMON_R0: R508.2, U2703.12
IMON_R1: R608.2, U2703.11
IMON_R2: R708.2, U2703.10
IMON_R3: R808.2, U2703.9
J2_PRES: J2501.7, R2502.1
L0_AUX3V3: C1009.1, J1001.5, R1017.2
L0_LED_A: C1010.1, J1001.3, R1018.2
L0_LED_G: Q1001.1, R1019.2, R1020.1
L0_LED_K: J1001.4, Q1001.3
L0_MVBL: R1015.2, U1007.10
L0_QALPHA_F: R1005.1, U1005.5
L0_QBUSY_F: R1001.1, U1004.5
L0_QBUSY_R: R1007.1, U1005.9
L0_QULD_F: R1003.1, U1004.9
L0_QULD_R: R1009.1, U1006.5
L1_AUX3V3: C1109.1, J1101.5, R1117.2
L1_LED_A: C1110.1, J1101.3, R1118.2
L1_LED_G: Q1101.1, R1119.2, R1120.1
L1_LED_K: J1101.4, Q1101.3
L1_MVBL: R1115.2, U1107.10
L1_QALPHA_F: R1105.1, U1105.5
L1_QBUSY_F: R1101.1, U1104.5
L1_QBUSY_R: R1107.1, U1105.9
L1_QULD_F: R1103.1, U1104.9
L1_QULD_R: R1109.1, U1106.5
L2_AUX3V3: C1209.1, J1201.5, R1217.2
L2_LED_A: C1210.1, J1201.3, R1218.2
L2_LED_G: Q1201.1, R1219.2, R1220.1
L2_LED_K: J1201.4, Q1201.3
L2_MVBL: R1215.2, U1207.10
L2_QALPHA_F: R1205.1, U1205.5
L2_QBUSY_F: R1201.1, U1204.5
L2_QBUSY_R: R1207.1, U1205.9
L2_QULD_F: R1203.1, U1204.9
L2_QULD_R: R1209.1, U1206.5
L3_AUX3V3: C1309.1, J1301.5, R1317.2
L3_LED_A: C1310.1, J1301.3, R1318.2
L3_LED_G: Q1301.1, R1319.2, R1320.1
L3_LED_K: J1301.4, Q1301.3
L3_MVBL: R1315.2, U1307.10
L3_QALPHA_F: R1305.1, U1305.5
L3_QBUSY_F: R1301.1, U1304.5
L3_QBUSY_R: R1307.1, U1305.9
L3_QULD_F: R1303.1, U1304.9
L3_QULD_R: R1309.1, U1306.5
LATCH_TEST: R2412.1, TP2704.1, U1002.2, U1002.5, U1002.10, U1002.13, U1003.2, U1102.2, U1102.5, U1102.10, U1102.13, U1103.2, U1202.2, U1202.5, U1202.10, U1202.13, U1203.2, U1302.2, U1302.5, U1302.10, U1302.13, U1303.2, U2401.45
LEDA_GREEN: D2401.2, R2404.2
LEDA_RED: D2402.2, R2405.2
LED_AMPL: R2315.1, U2301.11, U2306.3
LED_FAULT_N: D2402.1, U2401.93
LED_FB: R2313.2, R2314.1, U2306.2
LED_STATUS_N: D2401.1, U2401.91
LED_STROBE: R1019.1, R1119.1, R1219.1, R1319.1, R2413.1, U2401.81
LID_G: C2219.1, Q2205.1, R2228.2, U2405.7
LID_IN: J2201.1, JP2201.1, R2227.2, R2228.1
LLD_F0: R128.2, R1011.1, U2401.59
LLD_F1: R228.2, R1111.1, U2401.60
LLD_F2: R328.2, R1211.1, U2401.61
LLD_F3: R428.2, R1311.1, U2401.62
LLD_R0: R528.2, R1012.1, U2401.1
LLD_R1: R628.2, R1112.1, U2401.2
LLD_R2: R728.2, R1212.1, U2401.3
LLD_R3: R828.2, R1312.1, U2401.4
LOOP_A: J2002.2, J2003.1
LOOP_B: J2003.2, J2004.1
LOOP_C: J2004.2, R2019.1
MON_ADC: C2707.1, C2708.1, D2701.3, R2704.2, U2401.30
MON_BUS: R2702.1, TP2701.1, U1007.8, U1107.8, U1207.8, U1307.8, U2704.3
MON_DRV: R2703.1, R2704.1, U2704.1, U2704.4
MON_EN_0: U1007.2, U2701.15
MON_EN_1: U1107.2, U2701.14
MON_EN_2: U1207.2, U2701.13
MON_EN_3: U1307.2, U2701.12
MON_EXT: R2408.1, U1007.15, U1107.15, U1207.15, U1307.15, U2405.4
MON_MUX_A0: U2401.92, U2701.1, U2703.1
MON_MUX_A1: U2401.94, U2701.2, U2703.16
MON_MUX_A2: U1007.1, U1107.1, U1207.1, U1307.1, U2401.96, U2703.15
MON_MUX_A3: U1007.16, U1107.16, U1207.16, U1307.16, U2401.67
MON_OUT: J2701.1, R2703.2
NRST: C2408.1, J2401.3, U2401.14
NTC_BOARD: C2222.1, R2231.2, RT2201.1, U2401.53
NTC_HTR: C2606.1, D2604.1, J2601.4, R2613.2, U2401.32
NTC_SIPM0: C1008.1, D1001.1, J1001.1, R1016.2, U2401.15
NTC_SIPM1: C1108.1, D1101.1, J1101.1, R1116.2, U2401.16
NTC_SIPM2: C1208.1, D1201.1, J1201.1, R1216.2, U2401.17
NTC_SIPM3: C1308.1, D1301.1, J1301.1, R1316.2, U2401.18
PULSER_A0: R2415.1, U2401.19, U2702.1
PULSER_A1: R2416.1, U2401.10, U2702.2
PULSER_A2: R2417.1, U2401.11, U2702.3
PULSER_AMPL: R109.1, R209.1, R309.1, R409.1, R509.1, R609.1, R709.1, R809.1, R2316.1, TP2702.1, U2302.10
PULSER_STROBE: R2411.1, TP2703.1, U101.5, U201.5, U301.5, U401.5, U501.5, U601.5, U701.5, U801.5, U2401.65
R0_A: C509.2, C510.2, D501.3, J501.1, R503.1, R504.1, R514.1
R0_CLLD: R528.1, U504.7, U1002.12
R0_CULD: U504.6, U1003.1
R0_FAST: C519.1, R522.1, R524.1, U503.1
R0_FCMP: D502.3, R524.2, R525.1, U504.1, U504.3
R0_FFB: C519.2, R522.2, R523.1, U503.4
R0_FS: C517.2, R520.2, R521.1, U503.3
R0_HV1: C501.1, R501.2, R502.1
R0_HVF: C502.1, J502.1, R502.2
R0_KLLD: U1002.11, U1005.11
R0_KULD: U1003.4, U1006.3
R0_MFAST: R525.2, U1007.5
R0_MPRE: R519.2, U1007.7
R0_PFB: R516.2, R517.1, U502.4
R0_PG: C516.1, R517.2
R0_PIN: C514.2, R515.1, U502.3
R0_PINA: C514.1, R514.2
R0_PRE: C517.1, R516.1, R518.1, R519.1, R520.1, U502.1
R0_PRE_TP: R518.2, TP501.1
R0_TL: C520.1, R526.2, U504.2
R0_TPG: R510.1, U501.7
R0_TPI: C509.1, C510.1, R511.2
R0_TPSW: R511.1, R512.1, U501.1
R0_TPV: C508.1, R509.2, U501.6
R0_TRIM: C503.1, C504.1, R503.2, R504.2, R505.2, R506.1
R0_TRIMDRV: C505.1, R505.1, R508.1, U1001.7
R0_TRIMFB: C505.2, R506.2, U1001.6
R0_TRIMIN: C506.1, R507.2, U1001.5
R0_TU: C521.1, R527.2, U504.4
R0_V5: C511.1, C515.1, C518.1, FB501.2, U502.5, U502.6, U503.5, U503.6
R0_VBL: C512.1, C513.1, R513.2, R515.2, R521.2, R523.2
R1_A: C609.2, C610.2, D601.3, J601.1, R603.1, R604.1, R614.1
R1_CLLD: R628.1, U604.7, U1102.12
R1_CULD: U604.6, U1103.1
R1_FAST: C619.1, R622.1, R624.1, U603.1
R1_FCMP: D602.3, R624.2, R625.1, U604.1, U604.3
R1_FFB: C619.2, R622.2, R623.1, U603.4
R1_FS: C617.2, R620.2, R621.1, U603.3
R1_HV1: C601.1, R601.2, R602.1
R1_HVF: C602.1, J602.1, R602.2
R1_KLLD: U1102.11, U1105.11
R1_KULD: U1103.4, U1106.3
R1_MFAST: R625.2, U1107.5
R1_MPRE: R619.2, U1107.7
R1_PFB: R616.2, R617.1, U602.4
R1_PG: C616.1, R617.2
R1_PIN: C614.2, R615.1, U602.3
R1_PINA: C614.1, R614.2
R1_PRE: C617.1, R616.1, R618.1, R619.1, R620.1, U602.1
R1_PRE_TP: R618.2, TP601.1
R1_TL: C620.1, R626.2, U604.2
R1_TPG: R610.1, U601.7
R1_TPI: C609.1, C610.1, R611.2
R1_TPSW: R611.1, R612.1, U601.1
R1_TPV: C608.1, R609.2, U601.6
R1_TRIM: C603.1, C604.1, R603.2, R604.2, R605.2, R606.1
R1_TRIMDRV: C605.1, R605.1, R608.1, U1101.7
R1_TRIMFB: C605.2, R606.2, U1101.6
R1_TRIMIN: C606.1, R607.2, U1101.5
R1_TU: C621.1, R627.2, U604.4
R1_V5: C611.1, C615.1, C618.1, FB601.2, U602.5, U602.6, U603.5, U603.6
R1_VBL: C612.1, C613.1, R613.2, R615.2, R621.2, R623.2
R2_A: C709.2, C710.2, D701.3, J701.1, R703.1, R704.1, R714.1
R2_CLLD: R728.1, U704.7, U1202.12
R2_CULD: U704.6, U1203.1
R2_FAST: C719.1, R722.1, R724.1, U703.1
R2_FCMP: D702.3, R724.2, R725.1, U704.1, U704.3
R2_FFB: C719.2, R722.2, R723.1, U703.4
R2_FS: C717.2, R720.2, R721.1, U703.3
R2_HV1: C701.1, R701.2, R702.1
R2_HVF: C702.1, J702.1, R702.2
R2_KLLD: U1202.11, U1205.11
R2_KULD: U1203.4, U1206.3
R2_MFAST: R725.2, U1207.5
R2_MPRE: R719.2, U1207.7
R2_PFB: R716.2, R717.1, U702.4
R2_PG: C716.1, R717.2
R2_PIN: C714.2, R715.1, U702.3
R2_PINA: C714.1, R714.2
R2_PRE: C717.1, R716.1, R718.1, R719.1, R720.1, U702.1
R2_PRE_TP: R718.2, TP701.1
R2_TL: C720.1, R726.2, U704.2
R2_TPG: R710.1, U701.7
R2_TPI: C709.1, C710.1, R711.2
R2_TPSW: R711.1, R712.1, U701.1
R2_TPV: C708.1, R709.2, U701.6
R2_TRIM: C703.1, C704.1, R703.2, R704.2, R705.2, R706.1
R2_TRIMDRV: C705.1, R705.1, R708.1, U1201.7
R2_TRIMFB: C705.2, R706.2, U1201.6
R2_TRIMIN: C706.1, R707.2, U1201.5
R2_TU: C721.1, R727.2, U704.4
R2_V5: C711.1, C715.1, C718.1, FB701.2, U702.5, U702.6, U703.5, U703.6
R2_VBL: C712.1, C713.1, R713.2, R715.2, R721.2, R723.2
R3_A: C809.2, C810.2, D801.3, J801.1, R803.1, R804.1, R814.1
R3_CLLD: R828.1, U804.7, U1302.12
R3_CULD: U804.6, U1303.1
R3_FAST: C819.1, R822.1, R824.1, U803.1
R3_FCMP: D802.3, R824.2, R825.1, U804.1, U804.3
R3_FFB: C819.2, R822.2, R823.1, U803.4
R3_FS: C817.2, R820.2, R821.1, U803.3
R3_HV1: C801.1, R801.2, R802.1
R3_HVF: C802.1, J802.1, R802.2
R3_KLLD: U1302.11, U1305.11
R3_KULD: U1303.4, U1306.3
R3_MFAST: R825.2, U1307.5
R3_MPRE: R819.2, U1307.7
R3_PFB: R816.2, R817.1, U802.4
R3_PG: C816.1, R817.2
R3_PIN: C814.2, R815.1, U802.3
R3_PINA: C814.1, R814.2
R3_PRE: C817.1, R816.1, R818.1, R819.1, R820.1, U802.1
R3_PRE_TP: R818.2, TP801.1
R3_TL: C820.1, R826.2, U804.2
R3_TPG: R810.1, U801.7
R3_TPI: C809.1, C810.1, R811.2
R3_TPSW: R811.1, R812.1, U801.1
R3_TPV: C808.1, R809.2, U801.6
R3_TRIM: C803.1, C804.1, R803.2, R804.2, R805.2, R806.1
R3_TRIMDRV: C805.1, R805.1, R808.1, U1301.7
R3_TRIMFB: C805.2, R806.2, U1301.6
R3_TRIMIN: C806.1, R807.2, U1301.5
R3_TU: C821.1, R827.2, U804.4
R3_V5: C811.1, C815.1, C818.1, FB801.2, U802.5, U802.6, U803.5, U803.6
R3_VBL: C812.1, C813.1, R813.2, R815.2, R821.2, R823.2
REF_BUF: R2310.1, U2305.1, U2305.2
RS485_DE: R2504.1, U2401.73, U2501.4, U2501.5
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
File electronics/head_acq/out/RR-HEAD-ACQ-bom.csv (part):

Refs,Qty,Value,Footprint,Manufacturer,MPN,DNP,Notes
C101 C201 C301 C401 C501 C601 C701 C801 C2204 C2213,10,1uF,Capacitor_SMD:C_1206_3216Metric,Murata,GRM31CR72A105KA01L,,
C102 C202 C302 C402 C502 C602 C702 C802 C2205,9,100nF,Capacitor_SMD:C_0603_1608Metric,Murata,GRM188R72A104KA35D,,
C103 C111 C203 C211 C303 C311 C403 C411 C503 C511 C603 C611 C703 C711 C803 C811 C2108 C2406,18,4.7uF,Capacitor_SMD:C_0603_1608Metric,Murata,GRM188R61A475KE15D,,
C104 C105 C106 C107 C108 C113 C114 C115 C118 C120 C121 C122 C125 C126 C127 C204 C205 C206 C207 C208 C213 C214 C215 C218 C220 C221 C222 C225 C226 C227 C304 C305 C306 C307 C308 C313 C314 C315 C318 C320 C321 C322 C325 C326 C327 C404 C405 C406 C407 C408 C413 C414 C415 C418 C420 C421 C422 C425 C426 C427 C504 C505 C506 C507 C508 C513 C514 C515 C518 C520 C521 C522 C604 C605 C606 C607 C608 C613 C614 C615 C618 C620 C621 C622 C704 C705 C706 C707 C708 C713 C714 C715 C718 C720 C721 C722 C804 C805 C806 C807 C808 C813 C814 C815 C818 C820 C821 C822 C1001 C1002 C1003 C1004 C1005 C1006 C1007 C1008 C1009 C1101 C1102 C1103 C1104 C1105 C1106 C1107 C1108 C1109 C1201 C1202 C1203 C1204 C1205 C1206 C1207 C1208 C1209 C1301 C1302 C1303 C1304 C1305 C1306 C1307 C1308 C1309 C2006 C2008 C2009 C2010 C2116 C2202 C2209 C2211 C2216 C2217 C2218 C2219 C2220 C2221 C2222 C2301 C2303 C2304 C2306 C2307 C2309 C2310 C2312 C2313 C2315 C2401 C2402 C2403 C2404 C2405 C2407 C2408 C2409 C2410 C2411 C2412 C2413 C2501 C2503 C2602 C2603 C2606 C2701 C2702 C2703 C2704 C2706,191,100nF,Capacitor_SMD:C_0402_1005Metric,Murata,GRM155R71C104KA88D,,"IB-21: zone identification input - function not available in rev A (part fitted, input idles high)."
C109 C209 C309 C409 C509 C609 C709 C809,8,100pF,Capacitor_SMD:C_0402_1005Metric,Murata,GRM1555C1H101FA01D,,
C110 C210 C310 C410 C510 C610 C710 C810,8,1nF,Capacitor_SMD:C_0402_1005Metric,Murata,GRM1555C1H102JA01D,DNP,
C112 C116 C212 C216 C312 C316 C412 C416 C512 C516 C612 C616 C712 C716 C812 C816 C2109 C2110 C2112 C2201 C2502,21,10uF,Capacitor_SMD:C_0805_2012Metric,Murata,GRM21BR61C106KE15L,,
C117 C217 C317 C417 C517 C617 C717 C817,8,220pF,Capacitor_SMD:C_0402_1005Metric,Murata,GRM1555C1H221JA01D,,
C119 C219 C319 C419 C519 C619 C719 C819,8,10pF,Capacitor_SMD:C_0402_1005Metric,Murata,GRM1555C1H100JA01D,,
C123 C223 C323 C423,4,1nF,Capacitor_SMD:C_0402_1005Metric,Murata,GRM1555C1H102JA01D,,
C124 C224 C324 C424,4,4.7nF,Capacitor_SMD:C_0402_1005Metric,Murata,GRM155R71H472KA01D,,
C1010 C1110 C1210 C1310 C2707,5,100pF,Capacitor_SMD:C_0402_1005Metric,Murata,GRM1555C1H101JA01D,,
C2001 C2102 C2103,3,100nF,Capacitor_SMD:C_0603_1608Metric,Murata,GRM188R71H104KA93D,,
C2002,1,22nF,Capacitor_SMD:C_0402_1005Metric,Murata,GRM155R71H223KA12D,,
C2003 C2004 C2005 C2601,4,10uF,Capacitor_SMD:C_1206_3216Metric,Murata,GRM31CR71E106KA12L,,
C2007 C2504 C2801 C2802 C2803 C2804,6,10nF,Capacitor_SMD:C_0603_1608Metric,Murata,GRM188R72A103KA01D,,
C2101,1,4.7uF,Capacitor_SMD:C_1206_3216Metric,Murata,GRM31CR71H475KA12L,,
C2104 C2105 C2107 C2111,4,22uF,Capacitor_SMD:C_0805_2012Metric,Murata,GRM21BR61A226ME44L,,
C2106,1,10pF,Capacitor_SMD:C_0402_1005Metric,Murata,GRM1555C1H100JA01D,DNP,
C2113 C2115 C2302 C2305 C2308 C2311 C2314,7,1uF,Capacitor_SMD:C_0603_1608Metric,Murata,GRM188R71C105KA12D,,
C2114 C2206 C2207 C2214 C2215 C2604 C2605 C2705,8,10nF,Capacitor_SMD:C_0402_1005Metric,Murata,GRM155R71H103KA88D,,
C2203,1,2.2uF,Capacitor_SMD:C_1210_3225Metric,Murata,GRM32ER72A225KA35L,,
C2208,1,1nF,Capacitor_SMD:C_0603_1608Metric,Murata,GRM188R72A102KA01D,,
C2210 C2212,2,470nF,Capacitor_SMD:C_0603_1608Metric,Murata,GRM188R71C474KA88D,,
C2708,1,100pF,Capacitor_SMD:C_0402_1005Metric,Murata,GRM1555C1H101JA01D,DNP,
D101 D201 D301 D401 D501 D601 D701 D801,8,BAV99,Package_TO_SOT_SMD:SOT-23,Nexperia,"BAV99,215",,
D102 D103 D202 D203 D302 D303 D402 D403 D502 D602 D702 D802 D2603 D2701,14,BAT54S,Package_TO_SOT_SMD:SOT-23,Nexperia,"BAT54S,215",,
D1001 D1101 D1201 D1301 D2002 D2003 D2004 D2502 D2604,9,PESD5V0S1BA,Diode_SMD:D_SOD-323,Nexperia,"PESD5V0S1BA,115",,"IB-21: zone identification input - function not available in rev A (part fitted, input idles high).; verify: true"
D2001 D2601,2,SMBJ16A,Diode_SMD:D_SMB,Littelfuse,SMBJ16A,,
D2201,1,PMEG10010ELR,Diode_SMD:D_SOD-123F,Nexperia,PMEG10010ELRX,,verify: true
D2202 D2602,2,BZX84-C12,Package_TO_SOT_SMD:SOT-23,Nexperia,"BZX84-C12,215",,
D2203,1,BAV199,Package_TO_SOT_SMD:SOT-23,Nexperia,"BAV199,215",,
D2401,1,green,LED_SMD:LED_0603_1608Metric,Lite-On,LTST-C191KGKT,,
D2402,1,red,LED_SMD:LED_0603_1608Metric,Lite-On,LTST-C191KRKT,,
D2501,1,SM712,Package_TO_SOT_SMD:SOT-23,Semtech,SM712.TCT,,
FB101 FB201 FB301 FB401 FB501 FB601 FB701 FB801 FB2101 FB2401,10,600R @100MHz,Inductor_SMD:L_0603_1608Metric,Murata,BLM18AG601SN1D,,
FB2201 FB2501,2,220R @100MHz,Inductor_SMD:L_0603_1608Metric,Murata,BLM18PG221SN1D,,
J101 J102 J201 J202 J301 J302 J401 J402 J501 J502 J601 J602 J701 J702 J801 J802 J2701,17,U.FL,Connector_Coaxial:U.FL_Hirose_U.FL-R-SMT-1_Vertical,Hirose,U.FL-R-SMT-1(10),,"1.25 mm high, mated 2.5 mm max; 60 V AC rated. Mate with I-PEX MHF I LK (locking) or U.FL-LP"
J1001 J1101 J1201 J1301,4,GH-6,Connector_JST:JST_GH_SM06B-GHS-TB_1x06-1MP_P1.25mm_Horizontal,JST,SM06B-GHS-TB(LF)(SN),,
J2001,1,Micro-Fit 3.0 1x8 RA,Connector_Molex:Molex_Micro-Fit_3.0_43650-0800_1x08_P3.00mm_Horizontal,Molex,43650-0800,,Mating: receptacle 43645-0800 + terminals 43030 (18-24 AWG variant for the heater pair). Seated height of the right-angle header is close to the 6.0 mm limit and is UNVERIFIED: see CONTRACT_CHANGE_REQUESTS.md CCR-HE-02 (local 8 mm zone or alternative).; verify: true
J2002 J2003 J2004,3,GH-4,Connector_JST:JST_GH_SM04B-GHS-TB_1x04-1MP_P1.25mm_Horizontal,JST,SM04B-GHS-TB(LF)(SN),,IB-21: zone identification (pins 3/4 AUX_N/AUX_GND -> BUMP_ZONE_x_N) NOT AVAILABLE IN REV A: the single-pole rail switches have no potential-free auxiliary contact; the inputs read 'not actuated'. Footprints and parts kept.
J2201,1,GH-2,Connector_JST:JST_GH_SM02B-GHS-TB_1x02-1MP_P1.25mm_Horizontal,JST,SM02B-GHS-TB(LF)(SN),,
J2402,1,GH-3,Connector_JST:JST_GH_SM03B-GHS-TB_1x03-1MP_P1.25mm_Horizontal,JST,SM03B-GHS-TB(LF)(SN),,
J2501,1,GH-8,Connector_JST:JST_GH_SM08B-GHS-TB_1x08-1MP_P1.25mm_Horizontal,JST,SM08B-GHS-TB(LF)(SN),,
J2601,1,Micro-Fit 3.0 1x6 RA,Connector_Molex:Molex_Micro-Fit_3.0_43650-0600_1x06_P3.00mm_Horizontal,Molex,43650-0600,,Mating: receptacle 43645-0600 + terminals 43030 (18-24 AWG variant for the heater pair). Seated height of the right-angle header is close to the 6.0 mm limit and is UNVERIFIED: see CONTRACT_CHANGE_REQUESTS.md CCR-HE-02 (local 8 mm zone or alternative).; verify: true
L2001,1,900R CM,rr_local:L_CommonMode_TDK_ACM4520,TDK,ACM4520-901-2P-T000,,pin pairing 1-2 / 4-3 and current rating UNVERIFIED | stage 2: land pattern from memory of the TDK ACM4520 outline (VERIFY against the TDK drawing; winding pairing 1-2 / 4-3 already UNVERIFIED in stage 1); verify: true
L2002,1,10uH,Inductor_SMD:L_Coilcraft_XAL4040-XXX,Coilcraft,XAL4040-103MEB,,verify: true
L2101 L2201,2,10uH,Inductor_SMD:L_Coilcraft_LPS4018,Coilcraft,LPS4018-103MRB,,verify: true
L2102 L2103,2,10uH,Inductor_SMD:L_1210_3225Metric,Murata,LQH32CN100K53L,,
Q1001 Q1101 Q1201 Q1301 Q2205 Q2602,6,BSS138,Package_TO_SOT_SMD:SOT-23,onsemi,BSS138LT1G,,
Q2201 Q2203 Q2204,3,BSS123,Package_TO_SOT_SMD:SOT-23,onsemi,BSS123LT1G,,
Q2202,1,MMBTA42,Package_TO_SOT_SMD:SOT-23,onsemi,MMBTA42LT1G,,
Q2601,1,SUD50P04-08,Package_TO_SOT_SMD:TO-252-2,Vishay,SUD50P04-08-GE3,,"SOA for a 3 ms, 15 V x 3 A linear transition must be checked against the datasheet curve; verify: true"
Q2603,1,MMBT3904,Package_TO_SOT_SMD:SOT-23,onsemi,MMBT3904LT1G,,
R101 R201 R301 R401 R501 R601 R701 R801,8,1k,Resistor_SMD:R_0805_2012Metric,Yageo,RC0805FR-071KL,,
R102 R202 R302 R402 R502 R602 R702 R802,8,100R,Resistor_SMD:R_0603_1608Metric,Yageo,RC0603FR-07100RL,,
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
